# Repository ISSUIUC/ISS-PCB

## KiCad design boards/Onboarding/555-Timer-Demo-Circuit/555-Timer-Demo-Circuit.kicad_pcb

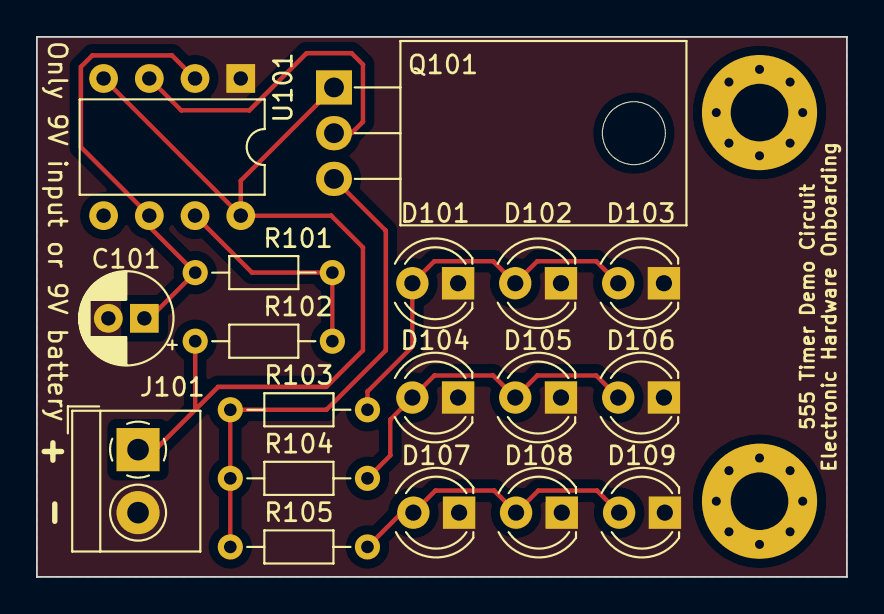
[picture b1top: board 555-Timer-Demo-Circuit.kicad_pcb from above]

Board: 2 copper layers, 45.0 x 30.0 mm, 20 parts (0 on the bottom side), 9 nets.

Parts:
C101: 10uf; CP_Radial_D5.0mm_P2.00mm
D101, D104, D107: Red; LED_D4.0mm
D102, D105, D108: Blue; LED_D4.0mm
D103, D106, D109: Green; LED_D4.0mm
H101, H102: MountingHole; MountingHole_3.2mm_M3_Pad_Via
J101: Terminal Block; TerminalBlock_4Ucon_1x02_P3.50mm_Horizontal
Q101: NMOS; TO-220-3_Horizontal_TabDown
R101, R102: 50K; R_Axial_DIN0204_L3.6mm_D1.6mm_P7.62mm_Horizontal
R103, R104, R105: 500; R_Axial_DIN0204_L3.6mm_D1.6mm_P7.62mm_Horizontal
U101: LM555xN; DIP-8_W7.62mm

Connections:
+9V: J101.1, Q101.1 (D), R102.1, U101.4 (R), U101.8 (VCC)
/THR: C101.1, R101.2, U101.2 (TR), U101.6 (THR)
GND: C101.2, D101.1 (K), D102.1 (K), D103.1 (K), D104.1 (K), D105.1 (K), D106.1 (K), D107.1 (K), D108.1 (K), D109.1 (K), J101.2, U101.1 (GND)
unnamed: D101.2 (A), D102.2 (A), D103.2 (A), R103.2
unnamed: D104.2 (A), D105.2 (A), D106.2 (A), R104.2
unnamed: D107.2 (A), D108.2 (A), D109.2 (A), R105.2
unnamed: Q101.2 (G), U101.3 (Q)
unnamed: Q101.3 (S), R103.1, R104.1, R105.1
unnamed: R101.1, R102.2, U101.7 (DIS)

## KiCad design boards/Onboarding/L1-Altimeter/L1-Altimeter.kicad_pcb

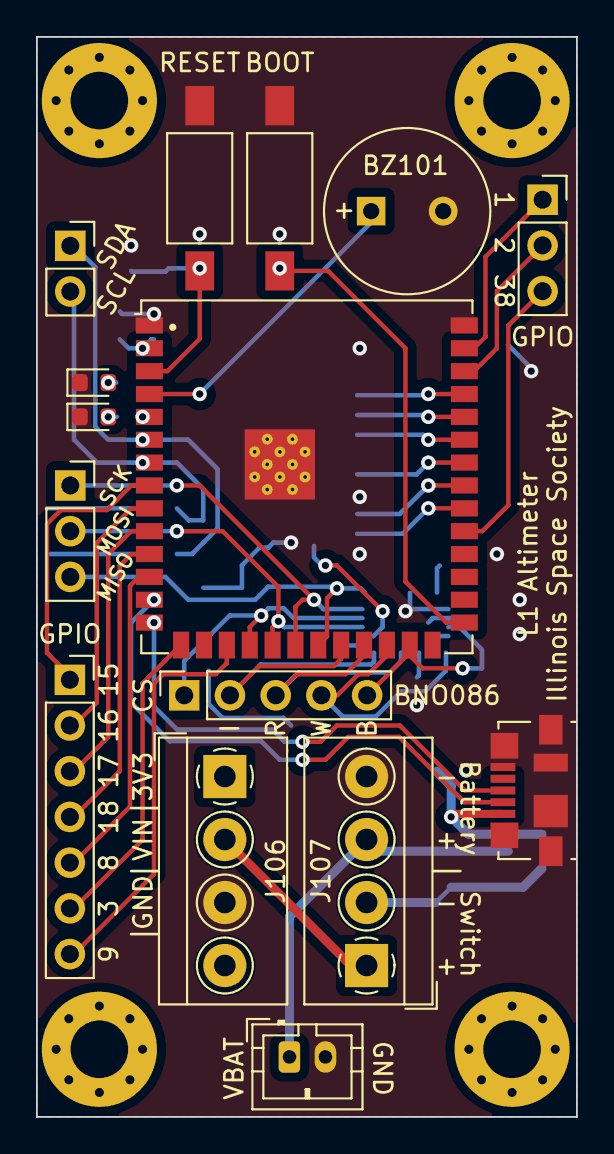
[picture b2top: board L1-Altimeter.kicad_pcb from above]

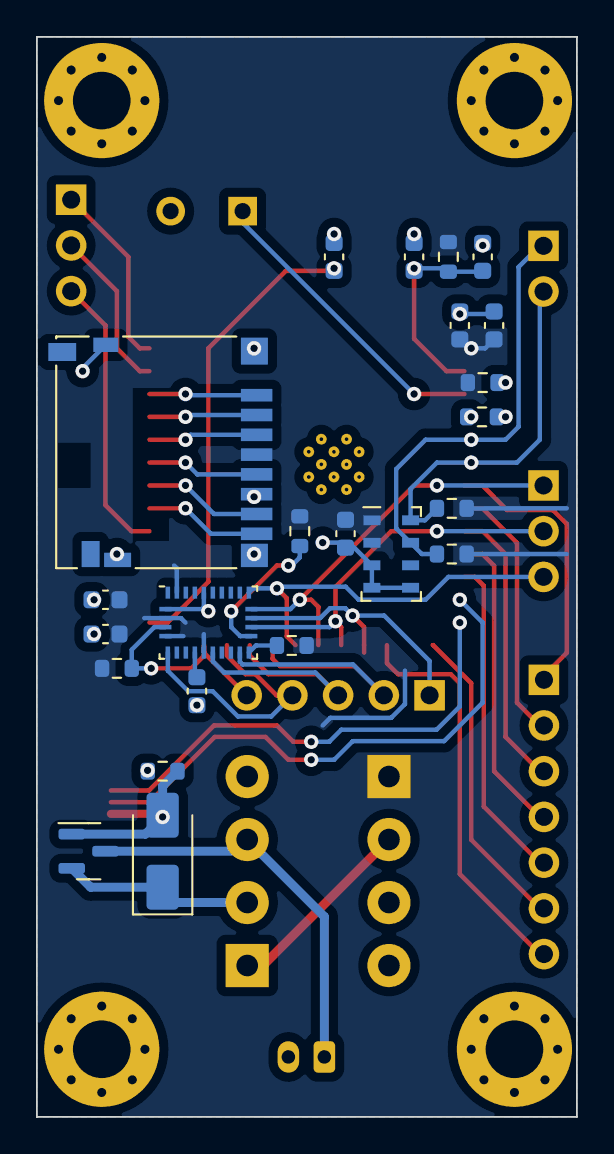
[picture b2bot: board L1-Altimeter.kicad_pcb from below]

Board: 2 copper layers, 30.0 x 60.0 mm, 42 parts (23 on the bottom side), 43 nets.

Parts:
BZ101: AT-0927-TT-6-R; MagneticBuzzer_PUI_AT-0927-TT-6-R
C101, C103, C104, C105, C106, C108, C109: 0.1uF; C_0603_1608Metric
C102: 22uF; C_0603_1608Metric
C107: 1uF; C_0603_1608Metric
D101: RED LED; LED_0603_1608Metric
D102: BLUE LED; LED_0603_1608Metric
D103: MBRA340; D_SMA
H101, H102, H103, H104: M3; MountingHole_3.2mm_M3_Pad_Via
J101: DM3D-SF; microSD_HC_Hirose_DM3D-SF
J102: Terminal Block; JST_PH_B2B-PH-K_1x02_P2.00mm_Vertical
J103: USB4105-GF-A; USB_Micro-B_Molex_47346-0001
J104: Conn_01x07; PinSocket_1x07_P2.54mm_Vertical
J105, J110: PinSocket_1x03_P2.54mm_Vertical
J106: Left; TerminalBlock_4Ucon_1x04_P3.50mm_Horizontal
J107: Right; TerminalBlock_4Ucon_1x04_P3.50mm_Horizontal
J108: Conn_01x05; PinSocket_1x05_P2.54mm_Vertical
J109: Conn_01x02; PinSocket_1x02_P2.54mm_Vertical
Q101: DMG2301L; SOT-23
R101, R102, R103, R107: 10k; R_0603_1608Metric
R104, R105: 470; R_0603_1608Metric
R106, R108: 2.2k; R_0603_1608Metric
R109: 100k; R_0603_1608Metric
SW101, SW102: SW_Push; SW_SPST_FSMSM
U101: ESP32-S3-WROOM-1U
U102: MS5611-01BA03; LGA-8_3x5mm_P1.25mm
U103: BNO086; LGA-28_5.2x3.8mm_P0.5mm

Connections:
+3V3: C102.1, C104.1, C105.1, C108.1, C109.1, J101.4 (VDD), J106.1, R101.2, R102.2, R103.2, R104.1, R106.2, R107.2, R108.2, U101.2 (3V3), U102.1 (VDD), U102.2 (PS), U103.3 (VDD), U103.5 (PS1), U103.10 (CLKSEL0), U103.28 (VDDIO)
/BNO086_BOOT: J108.5, R103.1, U101.25 (IO48), U103.4 (BOOTN)
/BNO086_CS: J108.1, U101.18 (IO10), U103.18 (H_CSN)
/BNO086_INT: J108.2, U101.22 (IO14), U103.14 (H_INTN)
/BNO086_RESET: J108.3, U101.23 (IO21), U103.11 (NRST)
/BNO086_WAKE: J108.4, U101.24 (IO47), U103.6 (PS0/WAKE)
/BOOT_SW: C101.2, SW101.2, U101.27 (IO0)
/BUZZER: BZ101.1 (-), U101.4 (IO4)
/GPIO1: J105.1, U101.39 (IO1)
/GPIO2: J105.2, U101.38 (IO2)
/GPIO3: J104.6, U101.15 (IO3)
/GPIO8: J104.5, U101.12 (IO8)
/GPIO9: J104.7, U101.17 (IO9)
/GPIO15: J104.1, U101.8 (IO15)
/GPIO16: J104.2, U101.9 (IO16)
/GPIO17: J104.3, U101.10 (IO17)
/GPIO18: J104.4, U101.11 (IO18)
/GPIO38: J105.3, U101.31 (IO38)
/I2C_SCL: J109.2, R102.1, U101.7 (IO7), U102.8 (SCLK)
/I2C_SDA: J109.1, R101.1, U101.6 (IO6), U102.7 (SDI/SDA)
/LED_BLUE: R105.1, U101.5 (IO5)
/MicroSD_CLK: J101.5 (CLK), U101.34 (IO41)
/MicroSD_CMD: J101.3 (CMD), U101.35 (IO42)
/MicroSD_DAT0: J101.7 (DAT0), U101.33 (IO40)
/MicroSD_DAT1: J101.8 (DAT1), U101.32 (IO39)
/MicroSD_DAT2: J101.1 (DAT2), U101.37 (TXD0)
/MicroSD_DAT3: J101.2 (DAT3/CD), U101.36 (RXD0)
/RESET_SW: C103.1, C107.1, R107.1, SW102.1, U101.3 (EN)
/SPI_MISO: J110.3, U101.21 (IO13), U103.20 (H_SDA/H_MISO/TX)
/SPI_MOSI: J110.2, U101.19 (IO11), U103.17 (H_SA0_MOSI)
/SPI_SCK: J110.1, U101.20 (IO12), U103.19 (H_SCL/SCK/RX)
/USB_D+: J103.3 (D+), U101.14 (IO20)
/USB_D-: J103.2 (D-), U101.13 (IO19)
/VBAT: J102.1, J107.3, Q101.3 (D)
/VBUS: D103.2 (A), J103.1 (VBUS), Q101.1 (G), R109.1
/VIN: J106.2, J107.1
/VSYS: D103.1 (K), J107.2, Q101.2 (S)
GND: BZ101.2 (+), C101.1, C102.2, C103.2, C104.2, C105.2, C106.2, C107.2, C108.2, C109.2, D101.1 (K), D102.1 (K), J101.6 (VSS), J101.11 (SHIELD), J102.2, J103.5 (GND), J103.6 (Shield), J106.3, J107.4, R109.2, SW101.1, SW102.2, U101.1 (GND), U101.40 (GND), U101.41 (EPAD), U102.3 (GND), U102.4 (CSB), U102.5 (CSB), U103.2 (GND), U103.25 (GNDIO)
unnamed: D101.2 (A), R104.2
unnamed: D102.2 (A), R105.2
unnamed: C106.1, U103.9 (CAP)
unnamed: R108.1, U103.15 (ENV_SCL)
unnamed: R106.1, U103.16 (ENV_SDA)

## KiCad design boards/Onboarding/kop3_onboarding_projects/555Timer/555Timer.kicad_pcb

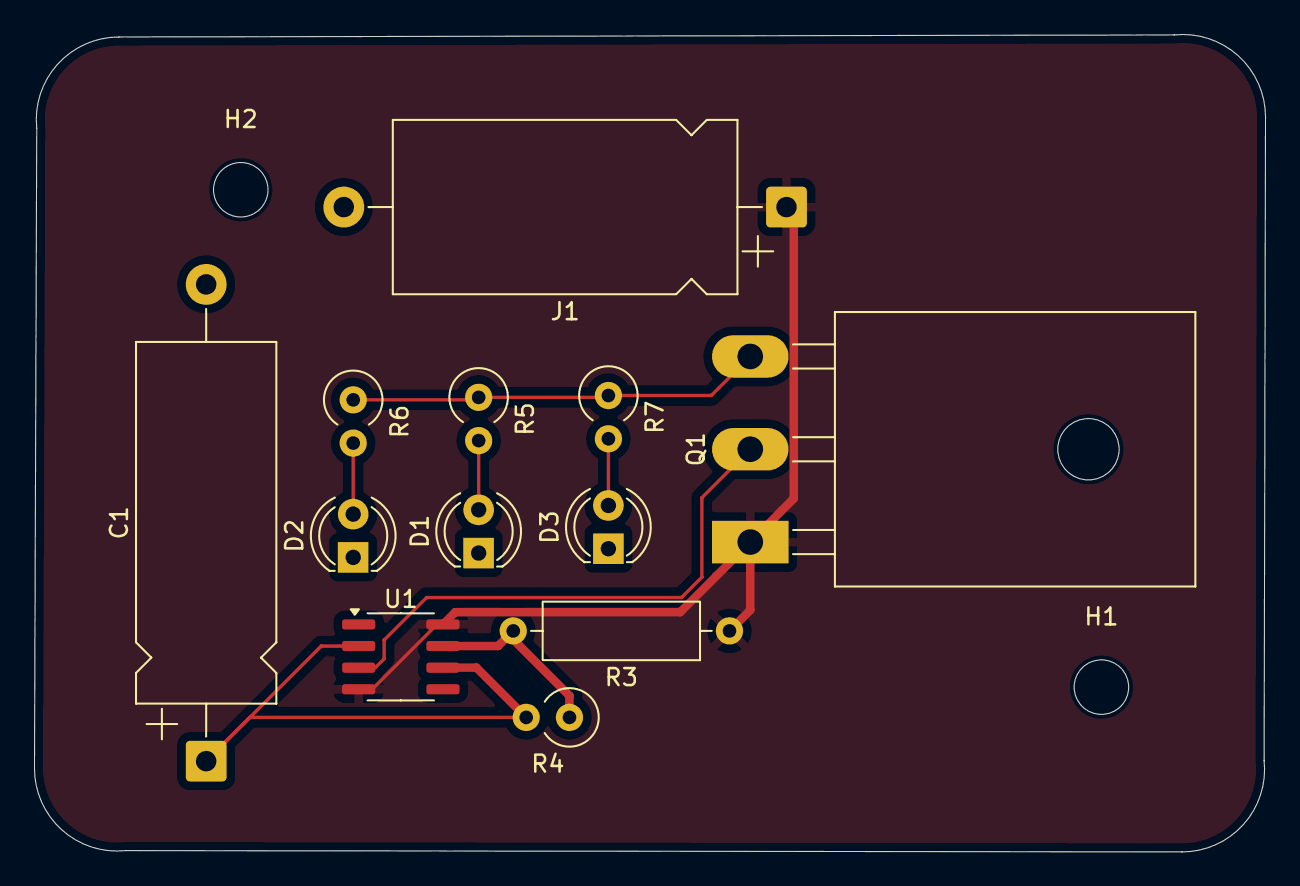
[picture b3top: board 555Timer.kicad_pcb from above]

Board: 2 copper layers, 72.3 x 48.0 mm, 14 parts (0 on the bottom side), 9 nets.

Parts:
C1: C_Polarized; CP_Axial_L21.0mm_D8.0mm_P28.00mm_Horizontal
D1: RED_LED; LED_D4.0mm
D2: GREEN_LED; LED_D4.0mm
D3: BLUE_LED; LED_D4.0mm
H1, H2: MountingHole; MountingHole_3.2mm_M3
J1: Conn_01x02; CP_Axial_L20.0mm_D10.0mm_P26.00mm_Horizontal
Q1: NMOS; TO-247-3_Horizontal_TabUp
R3: R_US; R_Axial_DIN0309_L9.0mm_D3.2mm_P12.70mm_Horizontal
R4: 50K; R_Axial_DIN0309_L9.0mm_D3.2mm_P2.54mm_Vertical
R5, R6, R7: 500; R_Axial_DIN0309_L9.0mm_D3.2mm_P2.54mm_Vertical
U1: LM555xM; SOIC-8_3.9x4.9mm_P1.27mm

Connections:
+9V: J1.1, Q1.1 (D), R3.1, U1.4 (R), U1.8 (VCC)
/THR: C1.1, R4.2, U1.2 (TR), U1.6 (THR)
GND: C1.2, D1.1 (K), D2.1 (K), D3.1 (K), J1.2, U1.1 (GND)
unnamed: D1.2 (A), R5.2
unnamed: D2.2 (A), R6.2
unnamed: D3.2 (A), R7.2
unnamed: Q1.2 (G), U1.3 (Q)
unnamed: Q1.3 (S), R5.1, R6.1, R7.1
unnamed: R3.2, R4.1, U1.7 (DIS)

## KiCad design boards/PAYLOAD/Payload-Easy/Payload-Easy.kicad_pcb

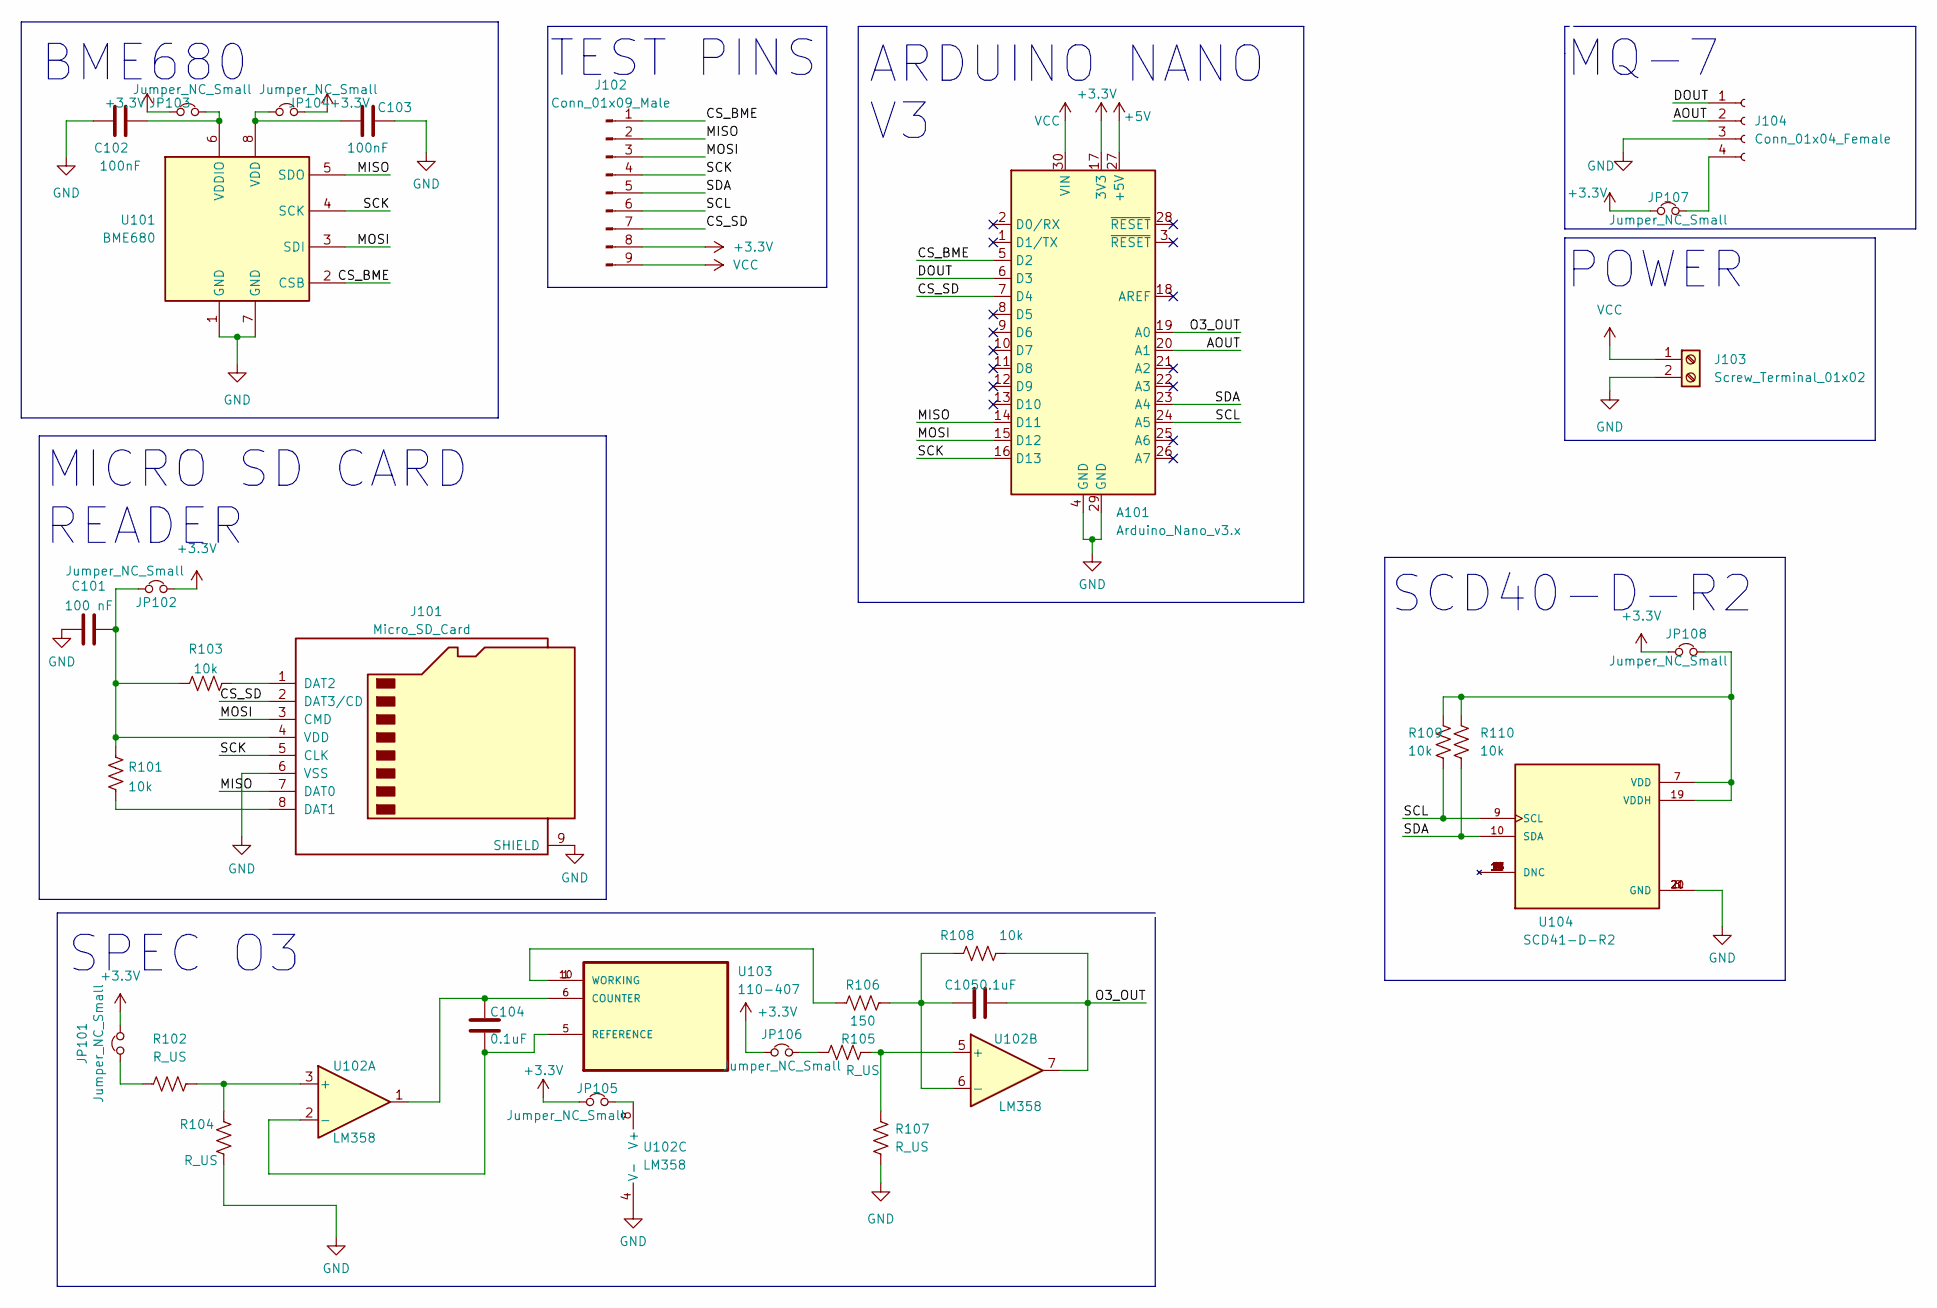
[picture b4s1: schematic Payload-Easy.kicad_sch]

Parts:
A101: Arduino_Nano_v3.x; Arduino_Nano
C101: 100 nF; C_0805_2012Metric
C102, C103: 100nF; C_0805_2012Metric
C104, C105: 0.1uF; C_0805_2012Metric
J101: Micro_SD_Card; microSD_HC_Hirose_DM3AT-SF-PEJM5
J102: Conn_01x09_Male; PinHeader_1x09_P2.54mm_Vertical
J103: Screw_Terminal_01x02; TerminalBlock_TE_282834-2_1x02_P2.54mm_Horizontal
J104: Conn_01x04_Female; PinSocket_1x04_P2.54mm_Horizontal
JP101, JP102, JP103, JP104, JP105, JP106, JP107, JP108: Jumper_NC_Small; SolderJumper-2_P1.3mm_Bridged_RoundedPad1.0x1.5mm
R101, R103, R108, R109, R110: 10k; R_0805_2012Metric
R102, R104, R105, R107: R_US; R_0805_2012Metric
R106: 150; R_0805_2012Metric
U101: BME680; Bosch_LGA-8_3x3mm_P0.8mm_ClockwisePinNumbering
U102: LM358
U103: 110-407; XDCR_110-407; PARTREV June 2017
U104: SCD41-D-R2; XDCR_SCD41-D-R2; PARTREV 1.2

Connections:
+3V3: A101.17 (3V3), J102.8, JP101.2, JP102.2, JP103.1, JP104.2, JP105.1, JP106.1, JP107.1, JP108.1
+5V: A101.27 (+5V)
/AOUT: A101.20 (A1), J104.2
/CS_BME: A101.5 (D2), J102.1, U101.2 (CSB)
/CS_SD: A101.7 (D4), J101.2 (DAT3/CD), J102.7
/DOUT: A101.6 (D3), J104.1
/MISO: A101.14 (D11), J101.7 (DAT0), J102.2, U101.5 (SDO)
/MOSI: A101.15 (D12), J101.3 (CMD), J102.3, U101.3 (SDI)
/O3_OUT: A101.19 (A0), C105.2, R108.2, U102.7
/SCK: A101.16 (D13), J101.5 (CLK), J102.4, U101.4 (SCK)
/SCL: A101.24 (A5), J102.6, R109.1, U104.9 (SCL)
/SDA: A101.23 (A4), J102.5, R110.2, U104.10 (SDA)
GND: A101.4 (GND), A101.29 (GND), C101.1, C102.1, C103.2, J101.6 (VSS), J101.9 (SHIELD), J103.2, J104.3, R104.2, R107.2, U101.1 (GND), U101.7 (GND), U102.4 (V-), U104.6 (GND), U104.20 (GND), U104.21 (GND)
unnamed: C101.2, J101.4 (VDD), JP102.1, R101.1, R103.1
unnamed: C102.2, JP103.2, U101.6 (VDDIO)
unnamed: C103.1, JP104.1, U101.8 (VDD)
unnamed: C104.1, U102.1, U103.6 (COUNTER)
unnamed: C104.2, U102.2 (-), U103.5 (REFERENCE)
unnamed: C105.1, R106.2, R108.1, U102.6 (-)
unnamed: J101.1 (DAT2), R103.2
unnamed: J101.8 (DAT1), R101.2
unnamed: J104.4, JP107.2
unnamed: JP101.1, R102.1
unnamed: JP105.2, U102.8 (V+)
unnamed: JP106.2, R105.1
unnamed: JP108.2, R109.2, R110.1, U104.7 (VDD), U104.19 (VDDH)
unnamed: R102.2, R104.1, U102.3 (+)
unnamed: R105.2, R107.1, U102.5 (+)
unnamed: R106.1, U103.1 (WORKING), U103.10 (WORKING)
VCC: A101.30 (VIN), J102.9, J103.1

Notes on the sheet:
MICRO SD CARD READER
MQ-7
SPEC O3
BME680
TEST PINS
SCD40-D-R2
POWER
ARDUINO NANO V3

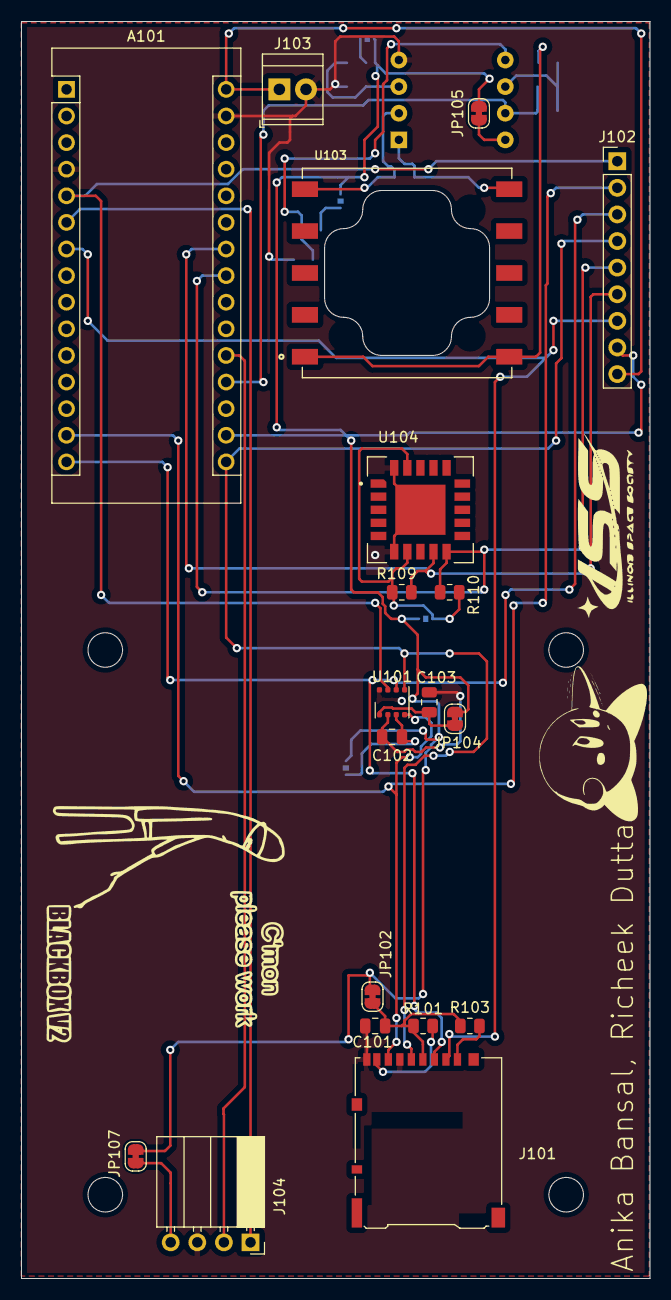
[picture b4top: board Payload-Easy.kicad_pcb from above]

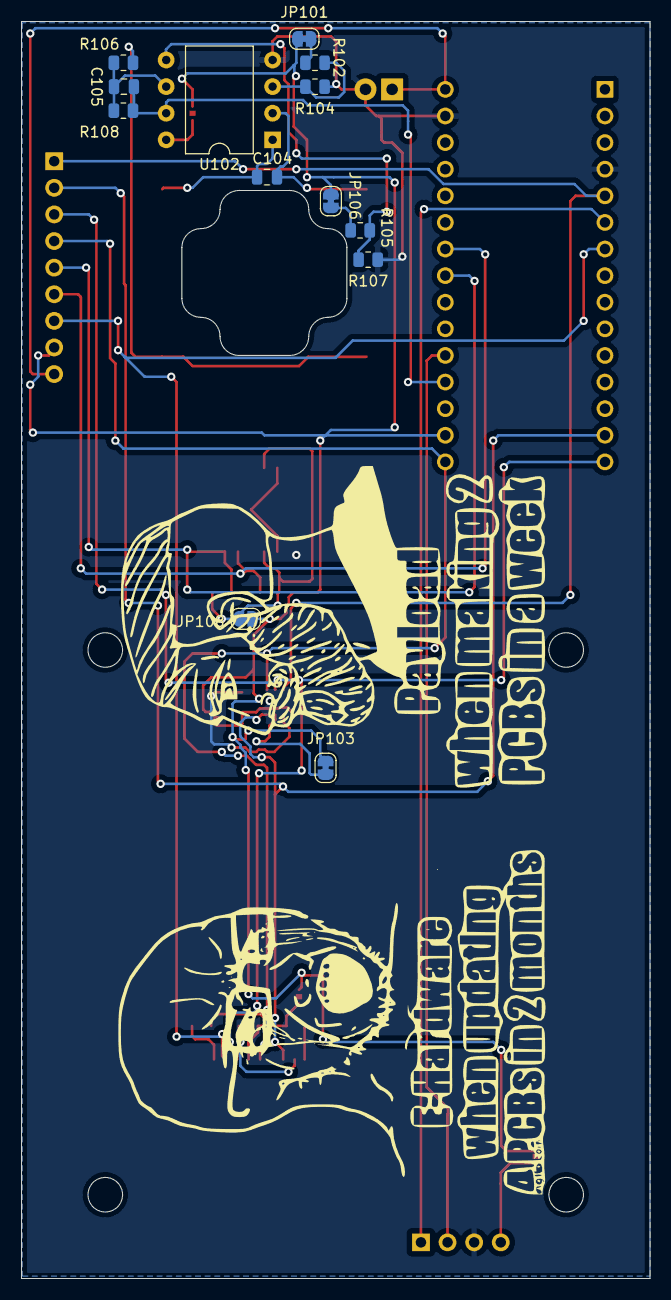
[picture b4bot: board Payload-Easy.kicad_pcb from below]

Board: 2 copper layers, 60.0 x 120.0 mm, 33 parts (13 on the bottom side), 29 nets.

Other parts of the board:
G: LOGO

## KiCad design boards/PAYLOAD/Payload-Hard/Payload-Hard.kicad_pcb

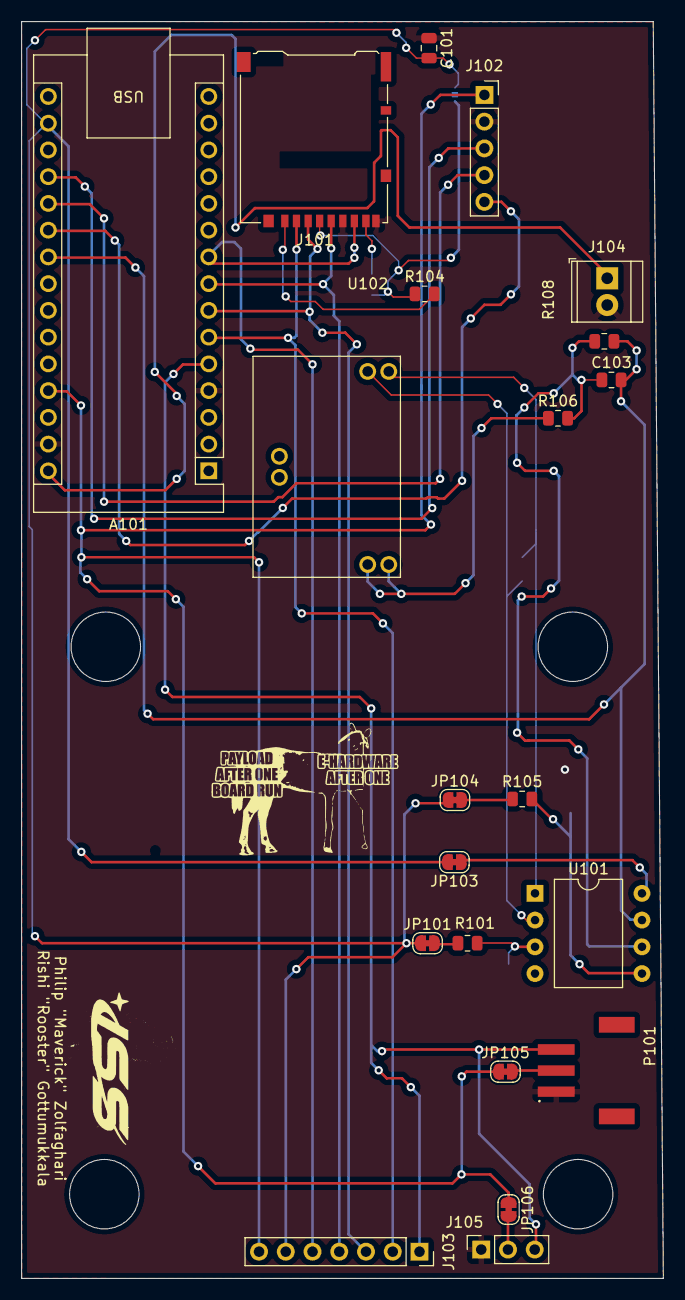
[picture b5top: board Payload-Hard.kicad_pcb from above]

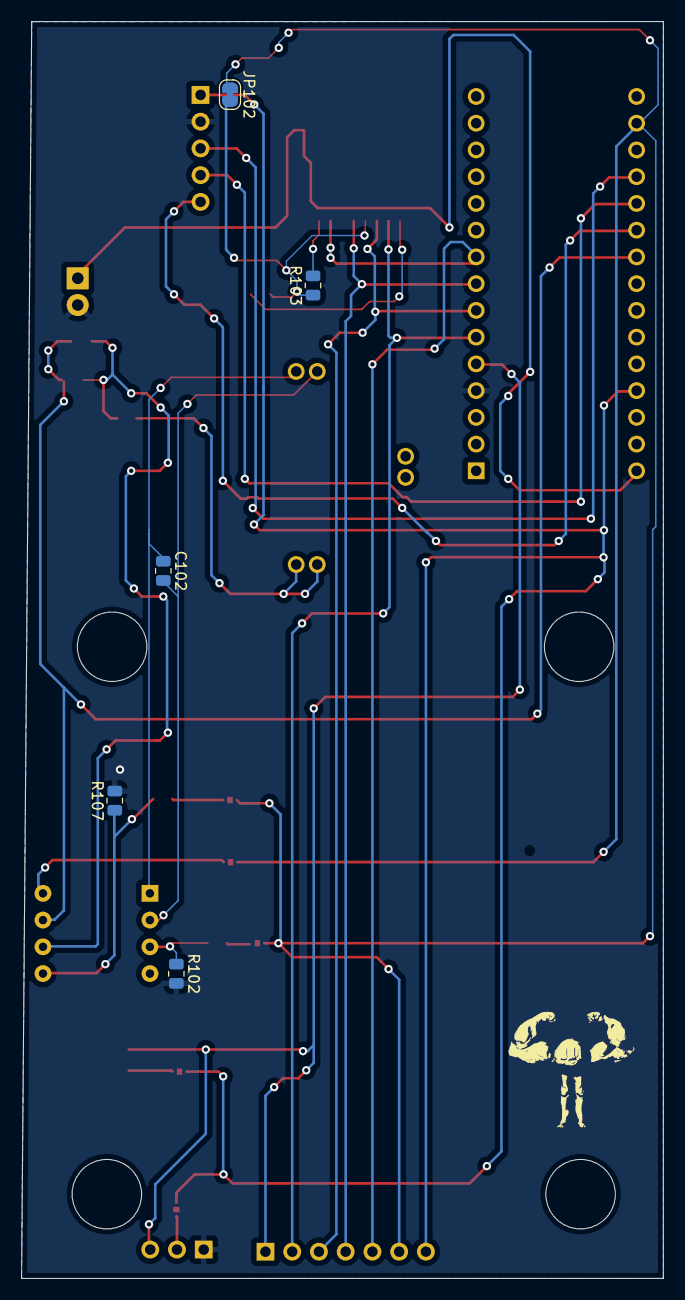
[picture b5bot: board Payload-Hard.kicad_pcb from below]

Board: 2 copper layers, 61.0 x 119.4 mm, 26 parts (5 on the bottom side), 27 nets.

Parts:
A101: Arduino_Nano_v3.x; Arduino_Nano
C101: 100 nF; C_0805_2012Metric
C102, C103: 0.1uF; R_0805_2012Metric
J101: Micro_SD_Card; microSD_HC_Hirose_DM3AT-SF-PEJM5
J102: Conn_01x05_Female; PinSocket_1x05_P2.54mm_Vertical
J103: Conn_01x07_Male; PinSocket_1x07_P2.54mm_Vertical
J104: Screw_Terminal_01x02; TerminalBlock_TE_282834-2_1x02_P2.54mm_Horizontal
J105: Conn_01x03_Female; PinSocket_1x03_P2.54mm_Vertical
JP101, JP102, JP103, JP104, JP105, JP106: SolderJumper_2_Bridged; SolderJumper-2_P1.3mm_Bridged_RoundedPad1.0x1.5mm
P101: S3B-PH-SM4-TB; JST_S3B-PH-SM4-TB
R101, R102, R105, R107, R108: R_US; R_0805_2012Metric
R103, R104: 10k; R_0805_2012Metric
R106: 150; R_0805_2012Metric
U101: LM358; DIP-8_W10.16mm
U102: 3SP_SO2_20

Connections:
/3V3: A101.17 (3V3), J103.6, JP101.1 (A), JP102.1 (A), JP103.2 (B), JP104.1 (A)
/5V: A101.27 (+5V), J102.1, J103.7, JP105.1 (A), JP106.1 (A)
/Counter: C102.1, U101.1, U102.5 (Counter)
/Dust_SIG: A101.5 (D2), J103.1, J105.3, P101.3
/NOX: A101.20 (A1), J102.4
/PRE: A101.21 (A2), J102.5
/RED: A101.19 (A0), J102.3
/Reference: C102.2, U101.2 (-), U102.4 (Reference)
/SO2_Out: A101.22 (A3), C103.2, R108.2, U101.7
/SPI_SDCARD_CS: A101.6 (D3), J101.2 (DAT3/CD), J103.2
/SPI_SDCARD_MISO: A101.9 (D6), J101.7 (DAT0), J103.5
/SPI_SDCARD_MOSI: A101.7 (D4), J101.3 (CMD), J103.3
/SPI_SDCARD_SCK: A101.8 (D5), J101.5 (CLK), J103.4
/Vbattery: A101.30 (VIN), J104.1
GND: A101.4 (GND), A101.29 (GND), C101.1, J101.6 (VSS), J101.9 (SHIELD), J102.2, J104.2, J105.1, P101.1, R102.2, R107.2
unnamed: C101.2, J101.4 (VDD), JP102.2 (B), R103.1, R104.1
unnamed: C103.1, R106.2, R108.1, U101.6 (-)
unnamed: J101.1 (DAT2), R104.2
unnamed: J101.8 (DAT1), R103.2
unnamed: JP101.2 (B), R101.1
unnamed: JP103.1 (A), U101.8 (V+)
unnamed: JP104.2 (B), R105.1
unnamed: JP105.2 (B), P101.2
unnamed: J105.2, JP106.2 (B)
unnamed: R101.2, R102.1, U101.3 (+)
unnamed: R105.2, R107.1, U101.5 (+)
unnamed: U102.1 (Working), U102.6 (Working)

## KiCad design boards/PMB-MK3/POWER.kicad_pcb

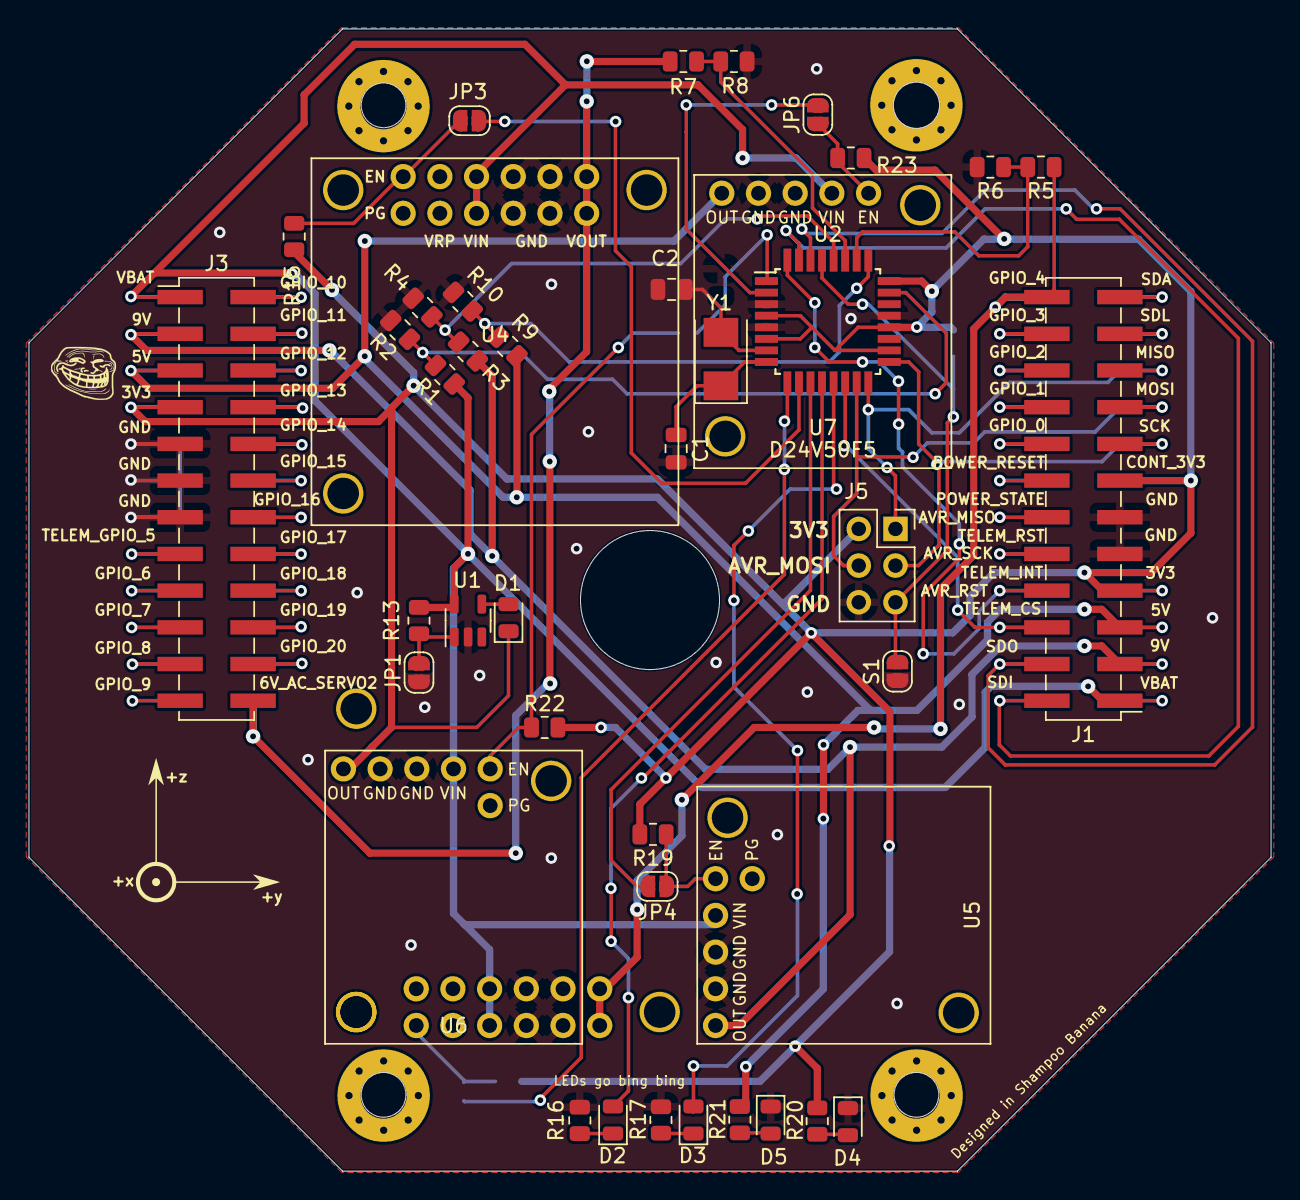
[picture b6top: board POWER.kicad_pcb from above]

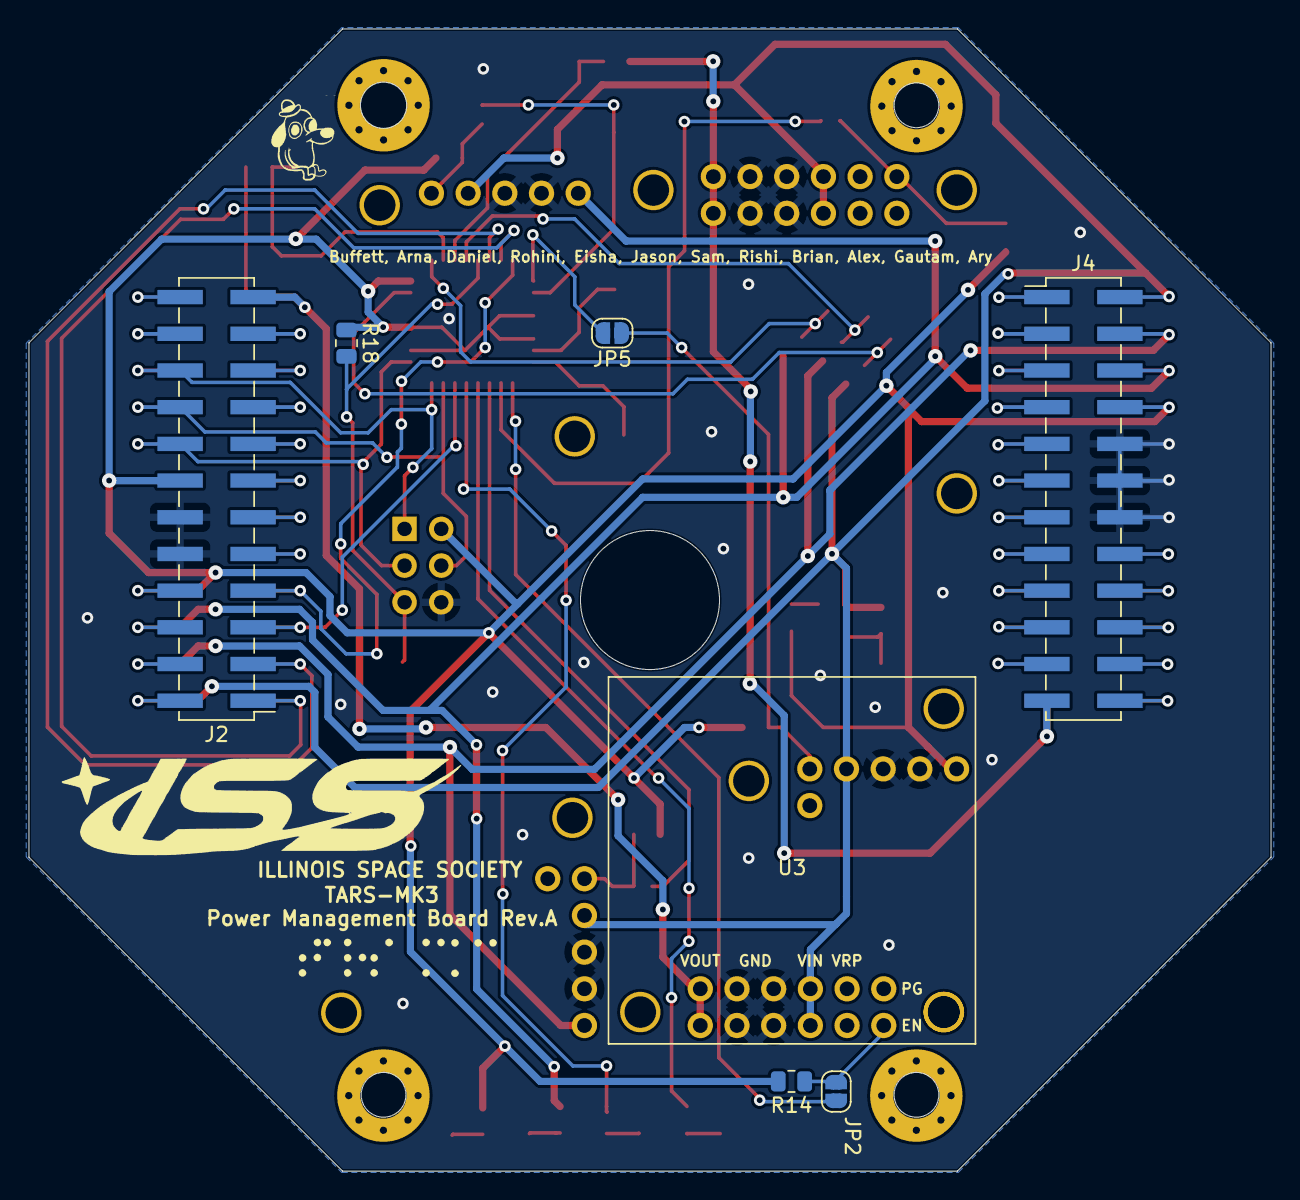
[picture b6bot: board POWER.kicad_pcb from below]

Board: 2 copper layers, 86.0 x 79.1 mm, 48 parts (7 on the bottom side), 65 nets.

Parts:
C1, C2: LOAD_C; C_0805_2012Metric
D1: D; D_0805_2012Metric
D2: GREEN; LED_0805_2012Metric
D3: ORANGE; LED_0805_2012Metric
D4: LED; LED_0805_2012Metric
D5: LED; D_0805_2012Metric
J1, J2, J3, J4: Conn_02x12_Odd_Even; PinHeader_2x12_P2.54mm_Vertical_SMD
J5: AVRISP; PinSocket_2x03_P2.54mm_Vertical
JP1, JP2, JP3, JP4, JP5, JP6: Jumper_2_Open; SolderJumper-2_P1.3mm_Open_RoundedPad1.0x1.5mm
R1, R3: 200kOhm; R_0805_2012Metric
R2, R4, R5, R6, R7, R8, R9, R10, R13, R14, R15, R19, R22, R23: 100kOhm; R_0805_2012Metric
R16, R17: 150Ω; R_0805_2012Metric
R18: 10k; R_0805_2012Metric
R20, R21: 1k; R_0805_2012Metric
S1: Reset; SolderJumper-2_P1.3mm_Open_RoundedPad1.0x1.5mm
U1: LK112M33TR; SOT-23-5
U2: ATmega328P-A; TQFP-32_7x7mm_P0.8mm
U3, U4: D36V50F6; D36V50F6-TARS
U5: D36V28F9; D36V28F3
U6: D36V28F3
U7: D24V50F5
Y1: 8Mhz; Crystal_SMD_5032-2Pin_5.0x3.2mm

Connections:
3V3: D1.1 (K), J1.7, J1.13, J2.8, J2.14, J3.7, J4.8, J5.2, R14.2, R15.2, R18.1, R19.2, R20.2, R22.2, R23.2, U2.4 (VCC), U2.6 (VCC), U2.18 (AVCC), U2.20 (AREF), U2.24 (PC1), U6.5 (OUT)
5V: J1.5, J2.6, J3.5, J4.6, R9.1, R21.1, U7.5 (OUT)
6V_AC_SERVO1: J1.24, J2.23, R5.1, U3.6 (VOUT), U3.12 (VOUT)
6V_AC_SERVO2: J3.24, J4.23, R7.1, U4.6 (VOUT), U4.12 (VOUT)
9V: J1.3, J2.4, J3.3, J4.4, R3.1, U5.5 (OUT)
/3V3_EN: JP5.2 (B), U2.1 (PD3)
/5V_EN: JP6.2 (B), U2.2 (PD4)
/5V_MONITOR: R9.2, R10.1, U2.25 (PC2)
/6V_AC_SERVO1_EN: JP2.2 (B), U2.9 (PD5)
/6V_AC_SERVO1_MONITOR: R5.2, R6.1, U2.26 (PC3)
/6V_AC_SERVO2_EN: JP3.2 (B), U2.10 (PD6)
/6V_AC_SERVO2_MONITOR: R7.2, R8.1, U2.27 (PC4)
/9V_EN: JP4.2 (B), U2.11 (PD7)
/9V_MONITOR: R3.2, R4.1, U2.28 (PC5)
/AVR_MISO: J1.19, J2.20, J5.1, U2.16 (PB4)
/AVR_MOSI: J1.17, J2.18, J5.4, U2.15 (PB3)
/AVR_RST: J5.5, R18.2, S1.2 (B), U2.29 (~RESET/PC6)
/AVR_SCK: J1.15, J2.16, J5.3, U2.17 (PB5)
/B2B_GPIO_6: J3.17, J4.18
/B2B_GPIO_7: J3.19, J4.20
/B2B_GPIO_8: J3.21, J4.22
/B2B_GPIO_9: J3.23, J4.24
/B2B_GPIO_10: J3.2, J4.1
/B2B_GPIO_11: J3.4, J4.3
/B2B_GPIO_12: J3.6, J4.5
/B2B_GPIO_13: J3.8, J4.7
/B2B_GPIO_14: J3.10, J4.9
/B2B_GPIO_15: J3.12, J4.11
/B2B_GPIO_16: J3.14, J4.13
/B2B_GPIO_17: J3.16, J4.15
/B2B_GPIO_18: J3.18, J4.17
/B2B_GPIO_19: J3.20, J4.19
/B2B_GPIO_20: J3.22, J4.21
/B2B_I2C_SCL: J1.21, J2.22
/B2B_I2C_SDA: J1.23, J2.24
/B2B_UART_SDI: J1.2, J2.1, U2.31 (PD1)
/B2B_UART_SDO: J1.4, J2.3, U2.30 (PD0)
/LED0: D2.2 (A), U2.12 (PB0)
/LED1: D3.2 (A), U2.13 (PB1)
/POWER_RESET: J1.14, J2.13
/POWER_STATE: J1.12, J2.11
/TELEM_CS: J1.6, J2.5, U2.14 (PB2)
/TELEM_GPIO_1: J1.16, J2.15
/TELEM_GPIO_2: J1.18, J2.17
/TELEM_GPIO_3: J1.20, J2.19
/TELEM_GPIO_4: J1.22, J2.21
/TELEM_GPIO_5: J3.15, J4.16
/TELEM_INT: J1.8, J2.7, U2.32 (PD2)
/TELEM_RST: J1.10, J2.9
/VBAT_MONITOR: R1.2, R2.1, U2.23 (PC0)
GND: C1.2, C2.2, D4.1 (K), D5.1 (K), J1.9, J1.11, J2.10, J2.12, J3.9, J3.11, J3.13, J4.10, J4.12, J4.14, J5.6, JP1.1 (A), R2.2, R4.2, R6.2, R8.2, R10.2, R16.2, R17.2, S1.1 (A), U1.2 (GND), U2.3 (GND), U2.5 (GND), U2.21 (GND), U3.4 (GND), U3.5 (GND), U3.10 (GND), U3.11 (GND), U4.4 (GND), U4.5 (GND), U4.10 (GND), U4.11 (GND), U5.3 (GND), U5.4 (GND), U6.3 (GND), U6.4 (GND), U7.3 (GND), U7.4 (GND)
unnamed: C1.1, U2.8 (XTAL2/PB7), Y1.1
unnamed: C2.1, U2.7 (XTAL1/PB6), Y1.2
unnamed: D1.2 (A), U1.4 (OUT)
unnamed: D2.1 (K), R16.1
unnamed: D3.1 (K), R17.1
unnamed: D4.2 (A), R20.1
unnamed: D5.2 (A), R21.2
unnamed: JP1.2 (B), R13.2, U1.1 (SHDN)
unnamed: JP2.1 (A), R14.1, U3.7 (EN)
unnamed: JP3.1 (A), R15.1, U4.7 (EN)
unnamed: JP4.1 (A), R19.1, U5.1 (EN)
unnamed: JP5.1 (A), R22.1, U6.1 (EN)
unnamed: JP6.1 (A), R23.1, U7.1 (EN)
VBAT: J1.1, J2.2, J3.1, J4.2, R1.1, R13.1, U1.5 (IN), U3.3 (VIN), U3.9 (VIN), U4.3 (VIN), U4.9 (VIN), U5.2 (VIN), U6.2 (VIN), U7.2 (VIN)
